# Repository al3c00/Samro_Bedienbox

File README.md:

# Samro_Bedienbox

## Übersicht:
Dieses Repository beinhaltet PCB-Daten (Gerber-Dateien und ein KiCAD-Projekt) sowie den Quellcode für die Programmierung des verwendeten ATMega328.

## Hintergrund:
Dies ist eine Steuerungsbox, die die bestehende Steuerung eines Samro Offsett KK Kartoffelvollernters ergänzt. Die Standardbedienung der 20 Jahre alten Maschine weicht von moderneren Bedienunglayouts ab. Um mir als Fahrer, der bei einem Lohnunternehmer im Herbst etliche Stunden mit neuen Maschinen fährt, jeweils den Wechsel der Maschine zu erleichtern, wurde diese Bedienung konstruiert. Die Funktionsbelegung ähnelt der Grimme GBX 800, wie sie beim Lohnunternehmen Wyss-Wyss verwendet wird.

## Funktion:
### Übersicht
Die Kontaktschalter der Samro-Bedienbox ziehen das Signal auf Masse. Die Hardware der Box erkennt dies und sendet ein entprechendes Signal an die Hauptplatine der Maschine. Die zusätzliche Bedienbox ergänzt diese FUnktionsweise. An die Signalpins der Kontaktschalter werden Kabel gelötet welche mit der zusätzlichen Box verbunden werden. 
### Detailiert
Beispielhafte Darstellung der Funktionsweise an einer Funktion:

```mermaid
  graph TD;
  Pin_MC_Samro-->Joystick;
  Joystick-->2N7002_zusätzliche_Box;
  ATMega328-->2N7002_zusätzliche_Box;
  2N7002_zusätzliche_Box-->Masse;
  Joystick-->Masse;

style Joystick fill:#4CED57
```

Um die Verwendung von ISP auf der Platine zun ermöglichen dürfen ISP-Pins des ATMega328 nicht belegt werden. Dies hat zur Folge, dass nicht alle wichtigen Funktionen der Maschine auf einer zusätzlichen Box belegt werden können. Abhilfe wird mit Jumpern geschaffen. Von zwei ATMega328 Ausgangspins (PD1 und PD2) kann ausgewählt werden, ob das Signal den Bunker oder die Dammaufnahme ansteuern soll. Andere Belegungsänderungen sind während Laufzeit nicht möglich und müssen durch ändern des Quellcodes und Neukompilierung gemacht werden.

## Software:
Es gibt kein seperater Ordner der für den Quellcode benutzt wird. Die .ino-Datei beinhaltet alle Daten. 

## Hardware:
Im Hardware-Ordner finden sich die Schemas, Gerber-Dateien und das dazugehörige KiCAD-Projekt. 

## Programmierung des ATMega328:
### Es gibt viele verschiedene, sehr gute Artikel dazu. Ein Beispiel: https://www.brennantymrak.com/articles/programming-avr-with-arduino

|ATMEga328|Arduino|
|----------|-------|
|PC6|Pin 10|
|PB5|Pin 13|
|PB4|Pin 12|
|PB3|Pin 11|
+ In IDE (Arduino IDE oder Visual Micro in VS2022), wähle Arduino als ISP
+ Richtiger Chip mit korrekter Clock-Speed

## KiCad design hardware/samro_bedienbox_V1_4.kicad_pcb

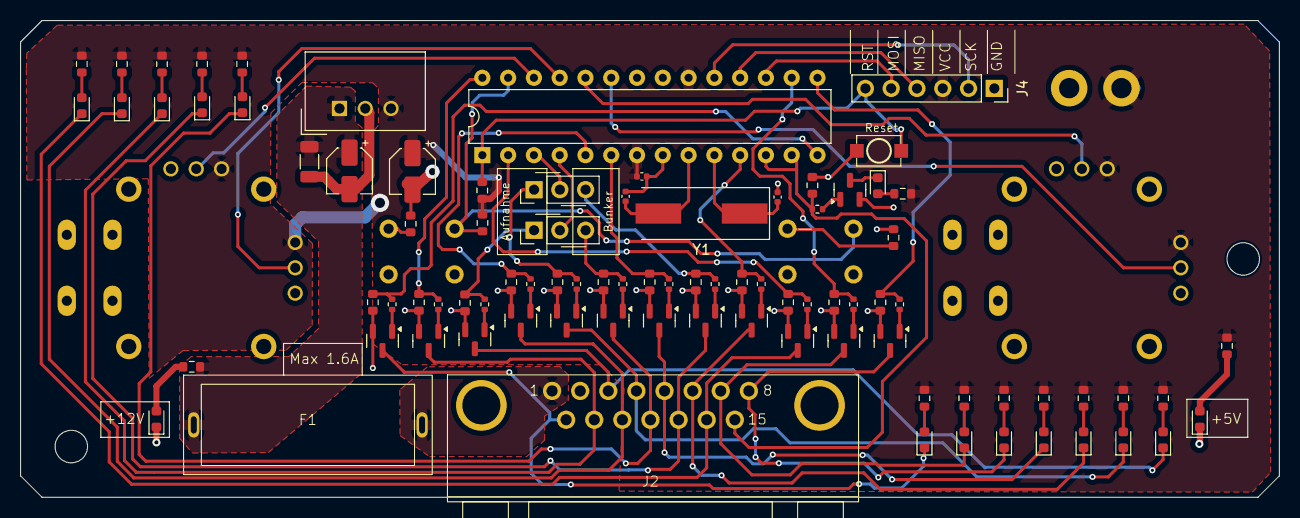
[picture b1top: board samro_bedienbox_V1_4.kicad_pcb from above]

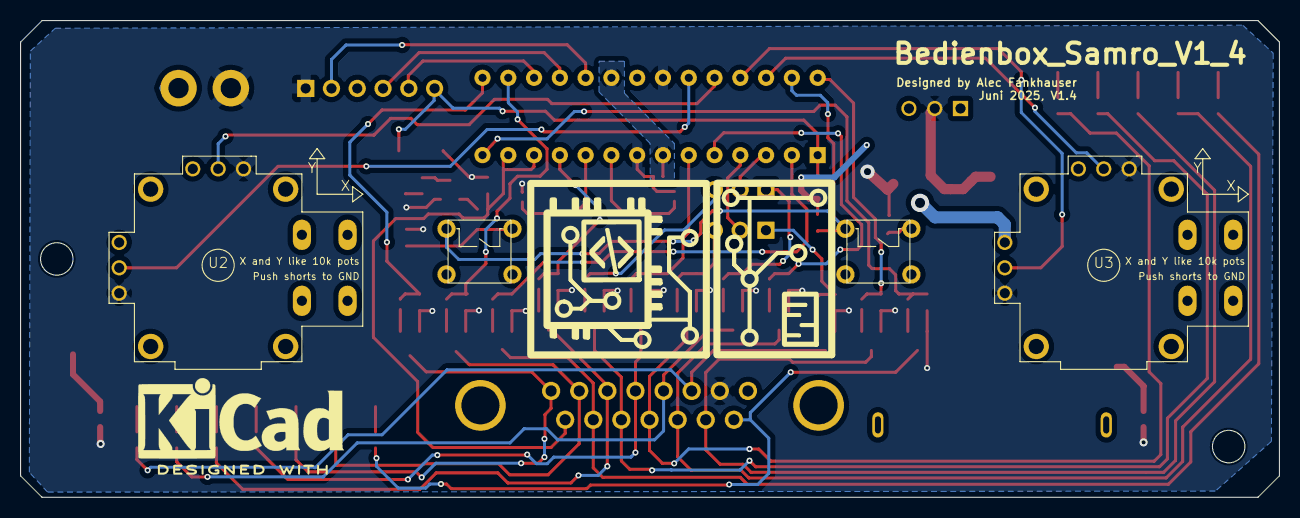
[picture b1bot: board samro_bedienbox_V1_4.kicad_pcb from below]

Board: 2 copper layers, 124.0 x 47.0 mm, 92 parts (4 on the bottom side), 73 nets.

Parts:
C1: 1uF; C_1206_3216Metric
C2: 100nF; C_0402_1005Metric
C3, C6: 10uF; CP_Elec_4x5.4
C4, C5: 20pF; C_0402_1005Metric
D1, D2, D3, D4, D5, D6, D7, D8, D9, D10, D11, D12, D13: LED_Red; LED_0603_1608Metric
D27, D28: LED_Green; LED_0603_1608Metric
F1: Fuseholder; Fuseholder_C58066
J2: D-Sub_15Pins; D-SUB-DR-15PCG-AB
J4: Conn_01x06_Socket; PinSocket_1x06_P2.54mm_Vertical
J5, J6: Conn_01x03_Pin; PinHeader_1x03_P2.54mm_Vertical
Q1, Q2, Q3, Q4, Q5, Q6, Q7, Q8, Q9, Q10, Q11, Q12, Q13: 2N7002K; SOT-23
R1, R4, R9, R10, R14, R17, R23, R24, R25, R26, R32, R36, R37: 220; R_0402_1005Metric
R2, R6, R11, R12, R15, R18, R27, R28, R29, R30, R33, R38, R39, R80: 130; R_0603_1608Metric
R3, R5, R7, R8, R13, R16, R19, R20, R21, R22, R31, R34, R35, R82, R83, R84: 10k; R_0603_1608Metric
R79: 470; R_0603_1608Metric
R85: 15k; R_0603_1608Metric
SW1: SW_Button_1; Button_DIP_DTS-62N
SW2: SW_Button_2; Button_DIP_DTS-62N
SW5: SW_Push; Button_L3.9_W3.0
U1: ATmega328P-P; DIP-28_W7.62mm
U2, U3: Analog_Thumb_Joystick
U4: TSR1-2450E; Converter_DCDC_TRACO_TSR1-xxxxE_THT
Y1: 16MHz; Crystal_SMD_HC49-SD

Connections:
/Signal.+12V: F1.2, J2.1
/Signal.Achse_Gerade: D5.1 (K), J2.7, Q5.3 (D)
/Signal.Achse_Links: D1.1 (K), J2.9, Q1.3 (D)
/Signal.Achse_Rechts: D2.1 (K), J2.8, Q2.3 (D)
/Signal.Bunker_Hoch: D8.1 (K), J2.13, Q8.3 (D)
/Signal.Bunker_Runter: D9.1 (K), J2.12, Q9.3 (D)
/Signal.Dammaufnahme_Hoch: D12.1 (K), J2.4, Q12.3 (D)
/Signal.Dammaufnahme_Runter: D13.1 (K), J2.3, Q13.3 (D)
/Signal.Deichsel_Links: D3.1 (K), J2.5, Q3.3 (D)
/Signal.Deichsel_Rechts: D4.1 (K), J2.6, Q4.3 (D)
/Signal.Rollboden_An: D6.1 (K), J2.14, Q6.3 (D)
/Signal.Schnabel_Hoch: D10.1 (K), J2.11, Q10.3 (D)
/Signal.Schnabel_Runter: D7.1 (K), J2.10, Q7.3 (D)
/Signal.Steuerbox_Aktiv: J2.15, R31.1, R32.1, U1.12 (PD6), U1.13 (PD7)
/Steuerbox_Links/12V_Protected: C1.1, C6.1, F1.1, R79.1, U4.1 (Vin)
/Steuerbox_Links/+5V: C2.1, C3.1, J4.3, R2.2, R6.2, R11.2, R12.2, R15.2, R18.2, R27.2, R28.2, R29.2, R30.2, R33.2, R38.2, R39.2, R80.2, R82.2, R83.2, U1.7 (VCC), U1.20 (AVCC), U2.1 (Y_VCC), U2.4 (X_VCC), U3.1 (Y_VCC), U3.4 (X_VCC), U4.3 (Vout)
/Steuerbox_Links/Button_Input: R83.1, SW1.1, SW2.1, U1.27 (PC4)
/Steuerbox_Links/ISP_MISO: J4.4, U1.18 (PB4)
/Steuerbox_Links/ISP_MOSI: J4.5, U1.17 (PB3)
/Steuerbox_Links/ISP_RESET: J4.6, R82.1, SW5.1, U1.1 (~RESET/PC6)
/Steuerbox_Links/ISP_SCK: J4.2, U1.19 (PB5)
/Steuerbox_Links/SW_Achse_Gerade: R13.1, R14.1, U1.16 (PB2)
/Steuerbox_Links/SW_Achse_Links: R1.1, R5.1, U1.14 (PB0)
/Steuerbox_Links/SW_Achse_Rechts: R3.1, R4.1, U1.15 (PB1)
/Steuerbox_Links/SW_Bunker_Hoch: J5.3, R20.1, R24.1
/Steuerbox_Links/SW_Bunker_Runter: J6.3, R21.1, R25.1
/Steuerbox_Links/SW_Dammaufnahme_Hoch: J5.1, R34.1, R36.1
/Steuerbox_Links/SW_Dammaufnahme_Runter: J6.1, R35.1, R37.1
/Steuerbox_Links/SW_Deichsel_Links: R7.1, R9.1, U1.6 (PD4)
/Steuerbox_Links/SW_Deichsel_Rechts: R8.1, R10.1, U1.11 (PD5)
/Steuerbox_Links/SW_FUNC1: J5.2, U1.3 (PD1)
/Steuerbox_Links/SW_FUNC2: J6.2, U1.4 (PD2)
/Steuerbox_Links/SW_Rollboden_An: R16.1, R17.1, U1.2 (PD0)
/Steuerbox_Links/SW_Schnabel_Hoch: R22.1, R26.1, U1.5 (PD3)
/Steuerbox_Links/SW_Schnabel_Runter: R19.1, R23.1, U1.28 (PC5)
/Steuerbox_Links/XTAL1: C4.2, U1.9 (XTAL1/PB6), Y1.2
/Steuerbox_Links/XTAL2: C5.2, U1.10 (XTAL2/PB7), Y1.1
GND: C1.2, C2.2, C3.2, C4.1, C5.1, C6.2, D27.1 (K), D28.1 (K), J2.2, J4.1, Q1.2 (S), Q2.2 (S), Q3.2 (S), Q4.2 (S), Q5.2 (S), Q6.2 (S), Q7.2 (S), Q8.2 (S), Q9.2 (S), Q10.2 (S), Q11.2 (S), Q12.2 (S), Q13.2 (S), R3.2, R5.2, R7.2, R8.2, R13.2, R16.2, R19.2, R20.2, R21.2, R22.2, R31.2, R34.2, R35.2, R84.1, R85.2, SW5.2, U1.8 (GND), U1.22 (GND), U2.3 (Y_GND), U2.6 (X_GND), U3.3 (Y_GND), U3.6 (X_GND), U4.2 (GND)
unnamed: D1.2 (A), R2.1
unnamed: D2.2 (A), R6.1
unnamed: D3.2 (A), R11.1
unnamed: D4.2 (A), R12.1
unnamed: D5.2 (A), R15.1
unnamed: D6.2 (A), R18.1
unnamed: D7.2 (A), R27.1
unnamed: D8.2 (A), R28.1
unnamed: D9.2 (A), R29.1
unnamed: D10.2 (A), R30.1
unnamed: D11.2 (A), R33.1
unnamed: D11.1 (K), Q11.3 (D)
unnamed: D12.2 (A), R38.1
unnamed: D13.2 (A), R39.1
unnamed: D27.2 (A), R80.1
unnamed: D28.2 (A), R79.2
unnamed: Q1.1 (G), R1.2
unnamed: Q2.1 (G), R4.2
unnamed: Q3.1 (G), R9.2
unnamed: Q4.1 (G), R10.2
unnamed: Q5.1 (G), R14.2
unnamed: Q6.1 (G), R17.2
unnamed: Q7.1 (G), R23.2
unnamed: Q8.1 (G), R24.2
unnamed: Q9.1 (G), R25.2
unnamed: Q10.1 (G), R26.2
unnamed: Q11.1 (G), R32.2
unnamed: Q12.1 (G), R36.2
unnamed: Q13.1 (G), R37.2
unnamed: R84.2, SW1.2
unnamed: R85.1, SW2.2
unnamed: U1.23 (PC0), U2.2 (Y_Out)
unnamed: U1.24 (PC1), U2.5 (X_Out)
unnamed: U1.25 (PC2), U3.2 (Y_Out)
unnamed: U1.26 (PC3), U3.5 (X_Out)

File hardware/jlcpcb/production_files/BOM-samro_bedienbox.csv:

Comment,Designator,Footprint,LCSC,Quantity
220,"R1,R10,R14,R17,R23,R24,R25,R26,R32,R36,R37,R4,R9",R_0402_1005Metric,C1091,13
2N7002K,"Q1,Q10,Q11,Q12,Q13,Q2,Q3,Q4,Q5,Q6,Q7,Q8,Q9",SOT-23,C114458,13
16MHz,Y1,Crystal_SMD_HC49-SD,C12676,1
10k,"R13,R16,R19,R20,R21,R22,R3,R31,R34,R35,R5,R7,R8,R82,R83,R84",R_0603_1608Metric,C15401,16
20pF,"C4,C5",C_0402_1005Metric,C1554,2
100nF,C2,C_0402_1005Metric,C1581,1
ATmega328P-P,U1,DIP-28_W7.62mm,C16653,1
1uF,C1,C_1206_3216Metric,C1848,1
D-Sub_15Pins,J2,D-SUB-DR-15PCG-AB,C19077347,1
LED_Red,"D1,D10,D11,D12,D13,D2,D3,D4,D5,D6,D7,D8,D9",LED_0603_1608Metric,C19171390,13
130,"R11,R12,R15,R18,R2,R27,R28,R29,R30,R33,R38,R39,R6,R80,R81",R_0603_1608Metric,C22796,15
15k,R85,R_0603_1608Metric,C22809,1
470,R79,R_0603_1608Metric,C23179,1
Conn_01x06_Socket,J4,PinSocket_1x06_P2.54mm_Vertical,C2832269,1
10uF,"C3,C6",CP_Elec_4x5.4,C3343,2
Conn_01x03_Pin,"J5,J6",PinHeader_1x03_P2.54mm_Vertical,C49257,2
Fuseholder,F1,Fuseholder_C58066,C58066,1
SW_Push,SW5,Button_L3.9_W3.0,C720477,1
TSR1-2450E,U4,Converter_DCDC_TRACO_TSR1-xxxxE_THT,,1
LED_Small,D29,LED_D3.0mm,,1
~,U3,Analog_Thumb_Joystick,,1
SW_Button_1,SW1,Button_DIP_DTS-62N,,1
LED_Small,D27,LED_D3.0mm,,1
~,U2,Analog_Thumb_Joystick,,1
LED_Small,D28,LED_D3.0mm,,1
SW_Button_2,SW2,Button_DIP_DTS-62N,,1

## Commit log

2025-06-23 .gitattributes, .gitignore und README.md hinzufügen.
2025-06-23 Projektdateien hinzufügen.
2025-06-26 Correct function mapping
2025-07-03 button input correct
2025-07-06 switched Rollboden und Achse_Gerade
2025-07-06 test
2025-07-06 improved loop, new output-values are only set when new input values are registered
2025-07-06 improved loop, output-values are only refreshed when new input values are registered
2025-07-06 push_everything
2025-07-06 refresh
2025-07-07 Mapping for left right side of cabin
2025-07-07 refresh_
2025-07-07 changed "Deichsel" to correct behavior (Input-->Output)
2025-12-02 Update README with project overview and functionality
    Added an overview and functionality description for the Samro Bedienbox project.
2025-12-02 Update README
    Added background and functionality details for the control box.
2025-12-02 Fix formatting issues in README section headers
2025-12-02 Update and rename
2025-12-02 Rename
2025-12-02 Update README
    Added section on programming the ATMega328.
2025-12-02 Add HW_version_1.0 hardware files
2025-12-02 Add HW_version_1_4_files
2025-12-02 add pictures and scheme
2025-12-02 Update README
    Added a reference article for programming the ATMega328.
2025-12-02 Revise ATmega328 to Arduino pin mapping format
    Updated the pin mapping table for ATmega328 and Arduino.
2025-12-02 Refactor ATMEga328 to Arduino pin mapping table
    Updated pin mapping table format for clarity.
2025-12-02 Fix formatting in README for ATmega328 table
2025-12-02 Fix wording in README for IDE instructions
2025-12-02 Fix formatting of programming section in README
2025-12-02 Enhance README with functionality details
    Added detailed overview and functionality description of the control box.
2025-12-02 Detailierter Funktionsbeschrieb
    Updated the diagram and added notes on ISP pin usage and jumper functionality.
2025-12-02 Update Pin_Controller to Pin_MC_Samro in diagram
2025-12-02 Fix typos and improve readability in README
    Korrigiert Rechtschreibfehler und verbessert die Lesbarkeit im README.
